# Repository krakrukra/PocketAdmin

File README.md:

# PocketAdmin  
  
#### Русская версия документации доступна [здесь](https://github.com/krakrukra/PocketAdmin/blob/master/extra/wiki/rus/README.md)  
  
This is a keystroke injection device (also called badusb). It is similar to a well-known  
[USB rubber ducky](https://shop.hak5.org/products/usb-rubber-ducky-deluxe) made by hak5, has rather extensive functionality, lower price  
and is also completely open source. It looks and feels like an ordinary USB flash drive,  
but acts as a keyboard that types in a preprogrammed payload. This payload can do anything  
from configuring a network to installing a reverse shell, since the device can basically  
do whatever an admin can with a terminal, but taking only a few seconds. This makes  
it a very powerful tool for automating sysadmin tasks or use in penetration testing.  

Here is quick summary of how PocketAdmin is different from other badusb devices:  
  
1. Made from inexpensive off-the-shelf parts, with not only open source firmware,  
but hardware design files as well. This allows the user to do substantial  
modifications to the design, as well as provides an option to build your own units.  
  
2. Has a built-in interpreter (compatible with older ducky script 1.0) which takes text files directly,  
so you never have to install any encoder software and keep converting payload.txt to inject.bin.  
  
3. Has USB mass storage capability, allowing for better payloads; the memory chip is integrated,  
so there is no need to keep sticking SD card in/out of various devices while developing payloads.  
  
4. Has an OS detection mechanism, which allows you to store multiple on-insertion payloads  
simultaneously and have the device automatically pick the correct payload to run.  
  
5. You can save up to 17 extra on-demand payloads and execute them by tapping on a capslock key  
the appropriate number of times. You can also use this functionality for more convenient device  
operation, such as rebooting into mass storage or DFU modes without taking the device apart.  
  
6. Uses extended set of commands for extra functionality, such as: mouse control, commands to  
hold and release keys, dynamic delays, ability to repeat blocks of commands; you can have  
several non-modifier keys pressed simultaneously and you are not limited in keyword order or by  
a set of hardcoded key combinations, only by the maximum of 10 commands on a single line.  
  
7. User has several configuration options available, none of which require a firmware update.  
You can set which serial number and VID / PID values to use, how the device should show up  
(keyboard+mouse+disk or keyboard+mouse only), change keyboard layout, hide a particular  
memory region on the USB disk, show fake storage capacity, make disk read-only, etc.  
  
8. Has a special HID-only method of exfiltrating data into a file, known as keystroke reflection.  
It allows to extract small amounts of data even from very restricted and air-gapped computers.  
  
**CHECK THE [WIKI](https://github.com/krakrukra/PocketAdmin/wiki) FOR HOW-TO-USE INFORMATION**  
  
---
  
## hardware
  
project is designed using KiCad 6.0.11  
check KiCad pcb file for PCB manufacturing info  
check KiCad sch file + BOM.txt for component info  
  
Uses integrated full-speed (12Mbit/s) USB2.0 peripheral, with  
96MiB of available on-board flash memory for data storage;  
measured speeds for MSD access: read 800-850 KiB/s, write 700-750 KiB/s   
  
There is an LED and a pushbutton on the device. The LED is a mass storage  
status indicator, which lights up any time the device reads or writes flash  
memory. It is recommended to make sure this LED is turned off before pulling  
the device out of host machine, to prevent filesystem corruption.  
The pushbutton on the device is referred to as MSD-only button. Normally  
the payload is run whenever you plug the device into a PC. But if you press  
and hold this button while inserting the device, it prevents any keystrokes  
from being typed in and makes the device show up as a flash drive. It also  
prevents use of features like hidden region, fake capacity, read-only mode.  
  
Fully assembled unit has dimensions of 59x18x9mm and weight of 8 grams.  
When opening up the case, be careful no to break the plastic studs near  
the USB connector and at the opposite (from USB) end of enclosure.  
  
hardware programmer device used in this project is [ST-Link V2](https://www.aliexpress.com/item/1823628996.html)  
For instructions on how to build and flash the device go check this video:  
[https://www.youtube.com/watch?v=cfud5Dq_w2M](https://www.youtube.com/watch?v=cfud5Dq_w2M)  
  
## firmware  
  
Programming language used = C  
Flashing software used = openocd 0.12.0  
IDE used = emacs text editor + Makefile  
  
The firmware was developed on debian 11.3 system, using gcc-arm-none-eabi  
toolchain (compiler, linker, binutils) and it does use gcc specific extentions.  
it was successfully compiled and tested with arm-none-eabi-gcc version 12.2.1  
  
Depends on libgcc.a, which is included in this repository. Linker script,  
startup code and openocd configuration files are included here as well.  
  
Files usb\_rodata.h, hid\_rodata.h, msd\_rodata.h are not really  
headers, but integral parts of usb.c, main.c, msd.c respectively.  
they are not intended to be included in any other files.  
  
For easy in-field updates, you can use the DFU bootloader. There is a dfu  
firmware image available in **/firmware/firmware\_RRNNN.dfu** file. The name  
format is this: RR stands for board revision (13 = rev 1.3) , NNN stands  
for firmware version. For example, firmware\_13005.dfu means board  
revision 1.3, firmware version 5  

To automate firmware build process you can use make utility. If you  
open terminal in **/firmware/** directory, you could run these commands:  
  
> make  
> make upload  
> make dfu  
> make clean  
  
"make" will compile source code and create several files, among them  
is firmware.bin which contains firmware to flash. "make upload" will  
flash this file via St-Link V2 programmer. Make sure to connect the  
programmer to the board properly, before you plug it into PC and run the  
command. "make dfu" will create a DFU firmware image from firmware.bin  
which can be used later by DFU flashing software. "make clean" will  
delete all the compiled or temporary files created by previous commands.  
  
## directories info

#### /firmware/ ------------- contains makefile, linker script, source files; this is a build directory  
/firmware/cmsis/ ------- header files from CMSIS compliant [STM32F0xx standard peripherals library](https://www.st.com/content/st_com/en/products/embedded-software/mcus-embedded-software/stm32-embedded-software/stm32-standard-peripheral-libraries/stsw-stm32048.html)  
/firmware/stdlib/ ---------- standard statically linked libraries (libgcc.a)  
/firmware/openocd/ ------- standard configuration files for openocd  
/firmware/fatfs/ ---------- [chan fatfs](http://www.elm-chan.org/fsw/ff/00index_e.html) filesystem module + custom W25N01GVZEIG disk driver  
/firmware/usb/ ------------ USB system, MSD and HID class device implementation  
/firmware/main/ ------- main application file, interrupt vector table, IRQ handlers and startup code  
/firmware/dfuse-pack.py ------- python script to create .dfu firmware images  
/firmware/linkScript.ld ------- custom linker script for the GNU linker (ld)  
/firmware/Makefile ------- file used by GNU make utility for build automation  
/firmware/firmware_13NNN.dfu ------ pre-compiled firmware image in DfuSe format (STM32)  
  
#### /hardware/ ------------------- contains KiCad project, schematic, PCB files  
/hardware/PocketAdmin.symbols/ -- project specific symbol library  
/hardware/PocketAdmin.pretty/ --- project specific footprint library  
/hardware/gerbers/ ----------- gerber+excellon fabrication output files  
/hardware/BOM.txt --------- list of parts needed for DIY assembly  
  
#### /extra/ -------------------  contains pictures, payload files, documents, etc.  
/extra/pictures/ ---------------- photos and mechanical drawings  
/extra/wiki/ ------------------ github wiki pages  
/extra/payloads/ ----------- example and test payloads for PocketAdmin  
/extra/payloads/FeatureTesting/fingerprinterTest/fingerdb/ -- example OS fingerprint database  
/extra/payloads/FeatureTesting/layoutTest/kblayout/ --- alternative keyboard layout files  
  
## contact info  
  
if you have a problem / question / feature request, here are your options for contacting me:  
send me an email to krakrukra@tutanota.com  
create a new github issue (check [closed issues](https://github.com/krakrukra/PocketAdmin/issues?q=is%3Aissue+is%3Aclosed) first)  
also, you can check out my [youtube channel](https://www.youtube.com/channel/UC8HZCV1vNmZvp7ci1vNmj7g)  
  
For extra security, you could use my PGP public key saved in [/extra/pubkey.asc](https://github.com/krakrukra/PocketAdmin/blob/master/extra/pubkey.asc).

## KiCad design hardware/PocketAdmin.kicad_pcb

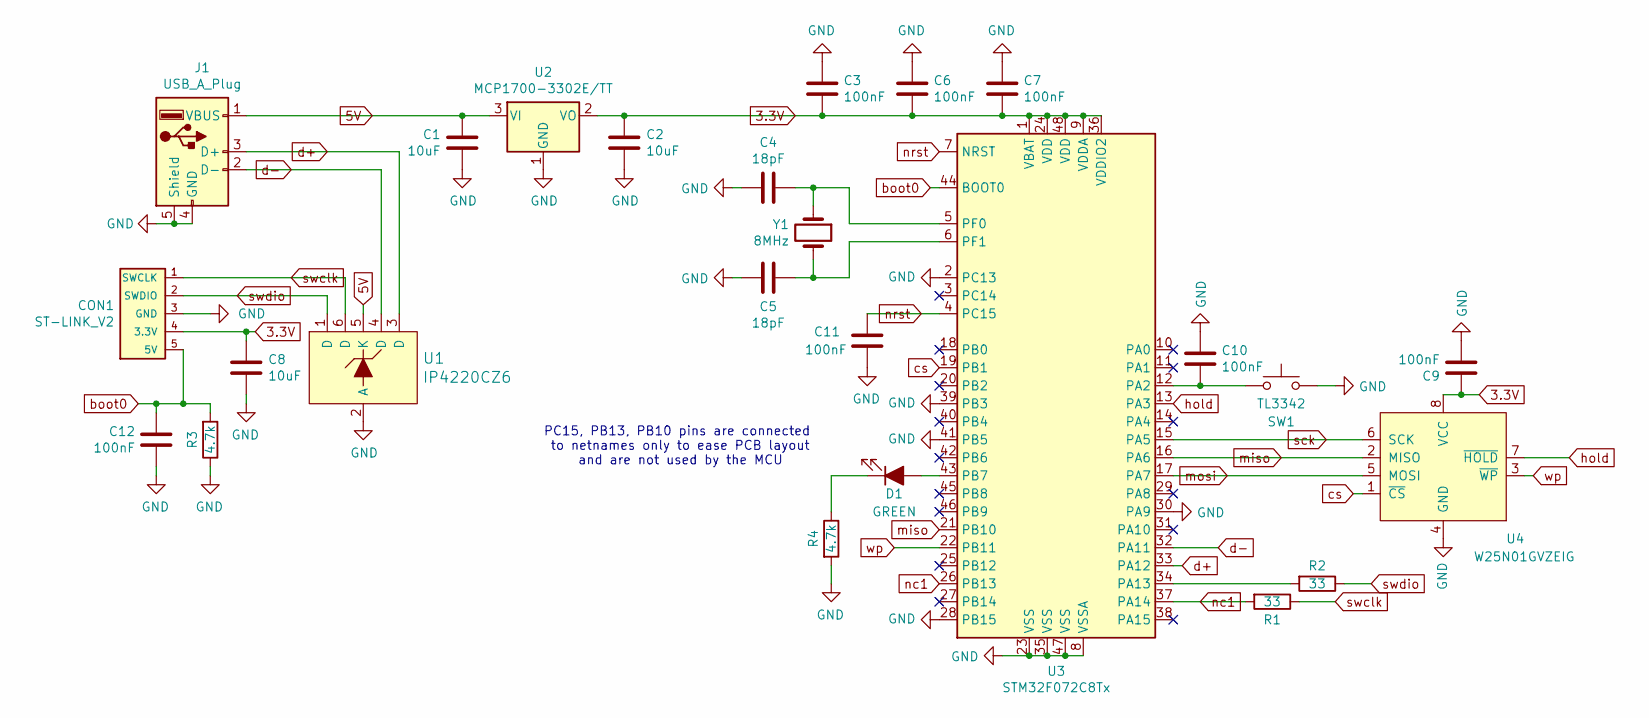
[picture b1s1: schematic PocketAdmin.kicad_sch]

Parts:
C1, C2, C8: 10uF; C_0805_2012Metric
C3, C6, C7, C9, C10, C11, C12: 100nF; C_0603_1608Metric
C4, C5: 18pF; C_0603_1608Metric
CON1: ST-LINK_V2; PinHeader_1x05_P2.54mm_Vertical
D1: GREEN; LED_0603_1608Metric
J1: USB_A_Plug; USB_A_CNCTech_1001-011-01101_Horizontal
R1, R2: 33; R_0603_1608Metric
R3, R4: 4.7k; R_0603_1608Metric
SW1: TL3342; SW_SPST_TL3342
U1: IP4220CZ6; TSOP-6_1.65x3.05mm_P0.95mm
U2: MCP1700-3302E/TT; SOT-23
U3: STM32F072C8Tx; LQFP-48_7x7mm_P0.5mm
U4: W25N01GVZEIG; WSON-8_8x6mm
Y1: 8MHz; Crystal_SMD_5032-2Pin_5.0x3.2mm

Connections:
3.3V: C2.1, C3.2, C6.2, C7.2, C8.1, C9.1, CON1.4 (3.3V), U2.2 (VO), U3.1 (VBAT), U3.9 (VDDA), U3.24 (VDD), U3.36 (VDDIO2), U3.48 (VDD), U4.8 (VCC)
5V: C1.1, J1.1 (VBUS), U1.5 (K), U2.3 (VI)
GND: C1.2, C2.2, C3.1, C4.2, C5.2, C6.1, C7.1, C8.2, C9.2, C10.1, C11.2, C12.1, CON1.3 (GND), J1.4 (GND), J1.5 (Shield), R3.1, R4.2, SW1.2, U1.2 (A), U2.1 (GND), U3.2 (PC13), U3.8 (VSSA), U3.23 (VSS), U3.28 (PB15), U3.30 (PA9), U3.35 (VSS), U3.39 (PB3), U3.41 (PB5), U3.47 (VSS), U4.4 (GND), U4.9 (GND)
unnamed: C4.1, U3.5 (PF0), Y1.1
unnamed: C5.1, U3.6 (PF1), Y1.2
unnamed: C10.2, SW1.1, U3.12 (PA2)
unnamed: D1.1 (K), R4.1
unnamed: D1.2 (A), U3.43 (PB7)
unnamed: R2.2, U3.34 (PA13)
boot0: C12.2, CON1.5 (5V), R3.2, U3.44 (BOOT0)
cs: U3.19 (PB1), U4.1 (~CS)
d+: J1.3 (D+), U1.3 (D), U3.33 (PA12)
d-: J1.2 (D-), U1.4 (D), U3.32 (PA11)
hold: U3.13 (PA3), U4.7 (~HOLD)
miso: U3.16 (PA6), U3.21 (PB10), U4.2 (MISO)
mosi: U3.17 (PA7), U4.5 (MOSI)
nc1: R1.2, U3.26 (PB13), U3.37 (PA14)
nrst: C11.1, U3.4 (PC15), U3.7 (NRST)
sck: U3.15 (PA5), U4.6 (SCK)
swclk: CON1.1 (SWCLK), R1.1, U1.6 (D)
swdio: CON1.2 (SWDIO), R2.1, U1.1 (D)
wp: U3.22 (PB11), U4.3 (~WP)

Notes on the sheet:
PC15, PB13, PB10 pins are connected to netnames only to ease PCB layout and are not used by the MCU

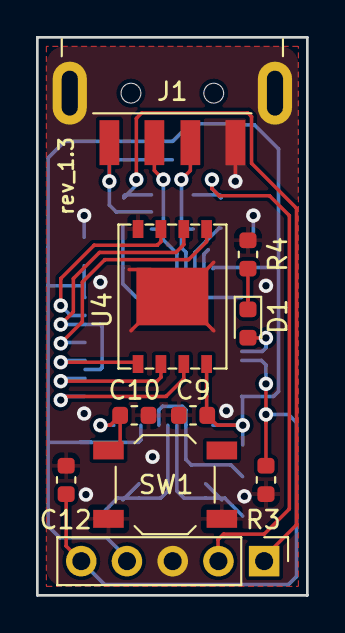
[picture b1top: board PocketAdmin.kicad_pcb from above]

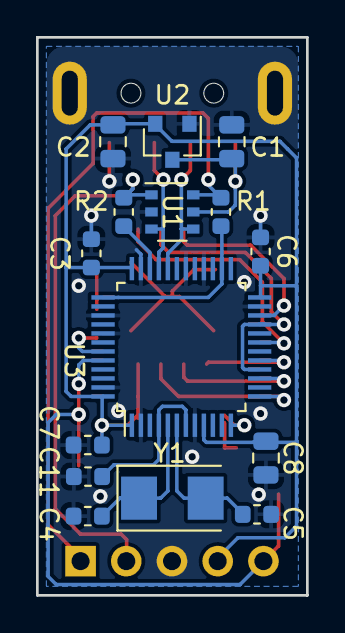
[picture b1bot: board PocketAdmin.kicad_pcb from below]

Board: 2 copper layers, 15.0 x 31.0 mm, 25 parts (15 on the bottom side), 22 nets.

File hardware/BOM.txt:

PocketAdmin_rev1.3 ----------------------- 28.11.2019 (dd.mm.yyyy)

all components, including mechanical ones are available on aliexpress.
example links to these items are for information purposes, check
for offers with better prices and shipping details yourself

quantities specified in this file are pieces per single PCB


STM32F072C8T6 microcontroller --- 1pcs

W25N01GVZEIG 128MiB flash memory chip --- 1pcs

IP4220CZ6 USB transient protection diode --- 1pcs

MCP1700-3302E/TT 3.3V LDO linear regulator --- 1pcs

0805 (2012 metric) 10% 16V X5R 10uF ceramic capacitors --- 3pcs

0603 (1608 metric) 5% 50V C0G 18pF ceramic capacitors --- 2pcs

0603 (1608 metric) 10% 50V X7R 100nF ceramic capacitors --- 7pcs

0603 (1608 metric) 5% 33 ohm resistors --- 2pcs

0603 (1608 metric) 5% 4.7k ohm resistors --- 2pcs

0603 (1608 metric) GREEN LED --- 1pcs

(5032 metric) NX5032GA STD-CSK-7 8MHz quartz crystal --- 1pcs

TL3342 tactile switch --- 1pcs
       you might want to choose similar ones with bigger height-off-PCB, up to 2mm (instead of 1.5mm with TL3342)
       https://www.aliexpress.com/item/32996664072.html

G49 black USB type A plug --- 1pcs
       https://www.aliexpress.com/item/32661919556.html

AK-N-52 black plastic enclosure --- 1pcs
       https://www.aliexpress.com/item/32849611612.html

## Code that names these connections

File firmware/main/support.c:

#include "../cmsis/stm32f0xx.h"

extern int main();
extern void usb_handler() __attribute__((interrupt));
extern void dma_handler() __attribute__((interrupt));

static void startup();
static inline void initialize_data(unsigned int* from, unsigned int* data_start, unsigned int* data_end) __attribute__((always_inline));
static inline void initialize_bss(unsigned int* bss_start, unsigned int* bss_end) __attribute__((always_inline));

static void default_handler() __attribute__((interrupt));
static void    tim7_handler() __attribute__((interrupt));

//these symbols are declared in the linker script
extern unsigned int __data_start__;//start of .data section in RAM
extern unsigned int __data_end__;//end of .data section in RAM
extern unsigned int __bss_end__;//end of .bss section in RAM
extern unsigned int __text_end__;//end of .text section in ROM

void* vectorTable[48] __attribute__(( section(".vectab,\"a\",%progbits@") )) =
  {
    (void*)0x20003FFC,//initial main SP value (16kB RAM size)
    (void*)&startup,//reset vector
    (void*)&default_handler,//NMI
    (void*)&default_handler,//HardFault
    (void*)0x00000000,//reserved
    (void*)0x00000000,//reserved
    (void*)0x00000000,//reserved
    (void*)0x00000000,//reserved
    (void*)0x00000000,//reserved
    (void*)0x00000000,//reserved
    (void*)0x00000000,//reserved
    (void*)&default_handler,//SVCall
    (void*)0x00000000,//reserved
    (void*)0x00000000,//reserved
    (void*)&default_handler,//PendSV
    (void*)&default_handler,//SysTick
    (void*)0x00000000,//IRQ0
    (void*)0x00000000,//IRQ1
    (void*)0x00000000,//IRQ2
    (void*)0x00000000,//IRQ3
    (void*)0x00000000,//IRQ4
    (void*)0x00000000,//IRQ5
    (void*)0x00000000,//IRQ6
    (void*)0x00000000,//IRQ7
    (void*)0x00000000,//IRQ8
    (void*)0x00000000,//IRQ9 
    (void*)&dma_handler,//IRQ10
    (void*)0x00000000,//IRQ11
    (void*)0x00000000,//IRQ12
    (void*)0x00000000,//IRQ13
    (void*)0x00000000,//IRQ14
    (void*)0x00000000,//IRQ15
    (void*)0x00000000,//IRQ16
    (void*)0x00000000,//IRQ17
    (void*)&tim7_handler,//IRQ18
    (void*)0x00000000,//IRQ19
    (void*)0x00000000,//IRQ20
    (void*)0x00000000,//IRQ21
    (void*)0x00000000,//IRQ22
    (void*)0x00000000,//IRQ23
    (void*)0x00000000,//IRQ24
    (void*)0x00000000,//IRQ25
    (void*)0x00000000,//IRQ26
    (void*)0x00000000,//IRQ27
    (void*)0x00000000,//IRQ28
    (void*)0x00000000,//IRQ29
    (void*)0x00000000,//IRQ30
    (void*)&usb_handler//IRQ31
  };

//copies initialized static variable values from ROM to RAM
static inline void initialize_data(unsigned int* from, unsigned int* data_start, unsigned int* data_end)
{
  while(data_start < data_end)
    {
      *data_start = *from;
      data_start++;
      from++;
    }
}

//writes to zero uninitialized static variable values in RAM
static inline void initialize_bss(unsigned int* bss_start, unsigned int* bss_end)
{
  while(bss_start < bss_end)
    {
      *bss_start = 0x00000000U;
      bss_start++;
    }
}

//the very first function that the CPU will run
static void startup()
{
  RCC->AHBENR |= (1<<18)|(1<<17)|(1<<0);//enable GPIOA, GPIOB, DMA clocks
  RCC->APB1ENR |= (1<<5)|(1<<4)|(1<<0);//enable TIM7, TIM6, TIM2 clocks
  RCC->APB2ENR |= (1<<12);//enable SPI1 clock
  
  GPIOB->MODER |= (1<<22)|(1<<14)|(1<<2);//PB11, PB7, PB1 are outputs
  GPIOB->BSRR = (1<<11)|(1<<1);//pull PB11, PB1 high (WP and SPI1 CS signals)  
  GPIOA->MODER |= (1<<15)|(1<<13)|(1<<11)|(1<<6);//PA3 is output; PA7, PA6, PA5 are in alternate function mode (SPI1)
  GPIOA->BSRR = (1<<3);//pull PA3 high (HOLD signal)
  GPIOA->PUPDR |= (1<<4);//enable pullup at PA2
  
  FLASH->ACR = (1<<4)|(1<<0);//enable prefetch buffer and insert 1 wait state for flash read access (because SYSCLK will be 48MHz)  
  
  RCC->CR |= (1<<19)|(1<<16);//enable HSE clock, clock security system
  while( !(RCC->CR & (1<<17)) );//wait until HSE is ready
  RCC->CFGR |= (1<<20)|(1<<16);//derive PLL clock from HSE, multiply HSE by 6 (8MHz * 6 = 48MHz)
  RCC->CR |= (1<<24);//enable PLL
  
  initialize_data(&__text_end__, &__data_start__, &__data_end__);
  initialize_bss(&__data_end__, &__bss_end__);
  
  while( !(RCC->CR & (1<<25)) );//wait until PLL is ready
  RCC->CFGR |= (1<<1);//set PLL as system clock  
  while( !((RCC->CFGR & 0x0F) == 0b1010) );//wait until PLL is used as system clock
  RCC->CR &= ~(1<<0);//disable HSI clock
  
  main();
  
  NVIC_SystemReset();//if main() ever returns reset MCU
  return;
}

//default IRQ handler initiates system reset
static void default_handler()
{
  NVIC_SystemReset();
  return;
}

//TIM7 is used for driving flash memory status LED
static void tim7_handler()
{
  GPIOB->BSRR = (1<<23);//turn the status LED off
  TIM7->SR = 0;//clear the overflow interrupt flag
  
  return;
}

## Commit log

2019-04-23 updated readme file
2019-05-15 USB reliability improvement
2019-05-15 documentation update
2019-05-22 added OS fingerprinter
2019-05-26 added layouts and documentation
2019-05-26 updated documentation
2019-05-26 updated pre-buil firmware image
2019-05-27 added HOLD and RELEASE commands
2019-05-29 documetation update
2019-05-30 small layout update
2019-06-19 simplified the use of modifier key commands
2019-06-21 small documentation update
2019-06-22 fixed one example script
2019-06-25 small readme update
2019-07-03 replaced tantalum capacitors with MLCC
2019-07-06 added panelised verison of PCB
2019-07-06 added panelised version of PCB
2019-07-08 changed pad connection from solid to thermal
2019-07-23 fixed a critical bug that led to device being bricked when config.txt had no newline at the end
2019-08-05 tiny documentation update
2019-08-11 better error handling for MSD interface
2019-08-11 cleaned up the readme file
2019-08-11 readme update
2019-08-11 readme pdate
2019-08-19 better explaination for MSD-only button use
2019-09-30 big speed and FTL update, see github issue
2019-10-14 readme.md update
2019-10-21 updated example payloads
2019-10-21 BOM.txt fix
2019-10-24 update example payloads
2019-10-26 new example payload
2019-10-26 fixed payload description
2019-10-26 fixed example payload
2019-11-06 some small fixes
2019-11-06 added a fancy shop link
2020-01-23 first testing release of 1.3 revision
2020-01-23 some fixes in wiki pages
2020-01-23 fixed some wiki pages
2020-01-23 fixed readme.md
2020-01-24 fix in dynamic startup delay
2020-02-03 added more keyboard layouts
2020-02-13 added PGP key
2020-02-15 replaced device photos
2020-02-29 added openbazaar links
2020-02-29 added openbazaar link
2020-04-25 some documentation fixes
2020-06-09 some bugfixes
2020-06-12 new payload updates
2020-06-15 changed compilation flags
2020-06-18 insert.ps1 will now delete cookies
2020-07-04 small change in documentation
2020-08-28 added Norwegian keyboard layout
2020-11-06 wiki update
2020-11-22 changed NRST capacitor
2020-12-08 added new ReverseOpenSSH payload
2020-12-09 ReverseOpenSSH payload update
2021-03-03 bugfix update, improved MAC compatibility
2021-04-04 Corrected path error in script
2021-08-11 prevent interpreter from freezing on error
2022-04-24 fixed typo
2022-04-29 added serbian keyboard layout
2022-05-07 added keypad and LED control commands
2022-10-26 payload update
2023-02-25 translated wiki
2023-02-25 fixed wiki links
2023-03-01 updated openocd scripts
2023-04-28 eject fix + keystroke reflection
2023-04-28 documentation fix
2023-11-15 move to newer toolchain versions
2024-02-10 added HID-only powershell payloads
2024-02-11 HIDrunlineScript payload fix
2024-02-13 add HID file exfiltration payload
2024-03-07 keystroke reflection payload now uses UTF8
2024-04-11 tiny PCB change to simplify manufacturing
2024-07-13 added READ_ONLY_MODE
2025-02-19 added MassGather payload
2025-10-31 added new payload
